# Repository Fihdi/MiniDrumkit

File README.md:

# 30hp Drumkit module

Eurorack DrumKit module with an Arduino Nano ESP32 3 channel wave-file player and analog Hi-Hat and Kick Drum sections.

The WAV Files are read from a microSD card and need to be called "1.wav", "2.wav" and "3.wav". The files need to be mono, encoded in 16-bit and have 16kHz sampling rate. You can use Audacity to export wav files in this format.

Demo Video: https://www.youtube.com/watch?v=cPHg9nKNO_o

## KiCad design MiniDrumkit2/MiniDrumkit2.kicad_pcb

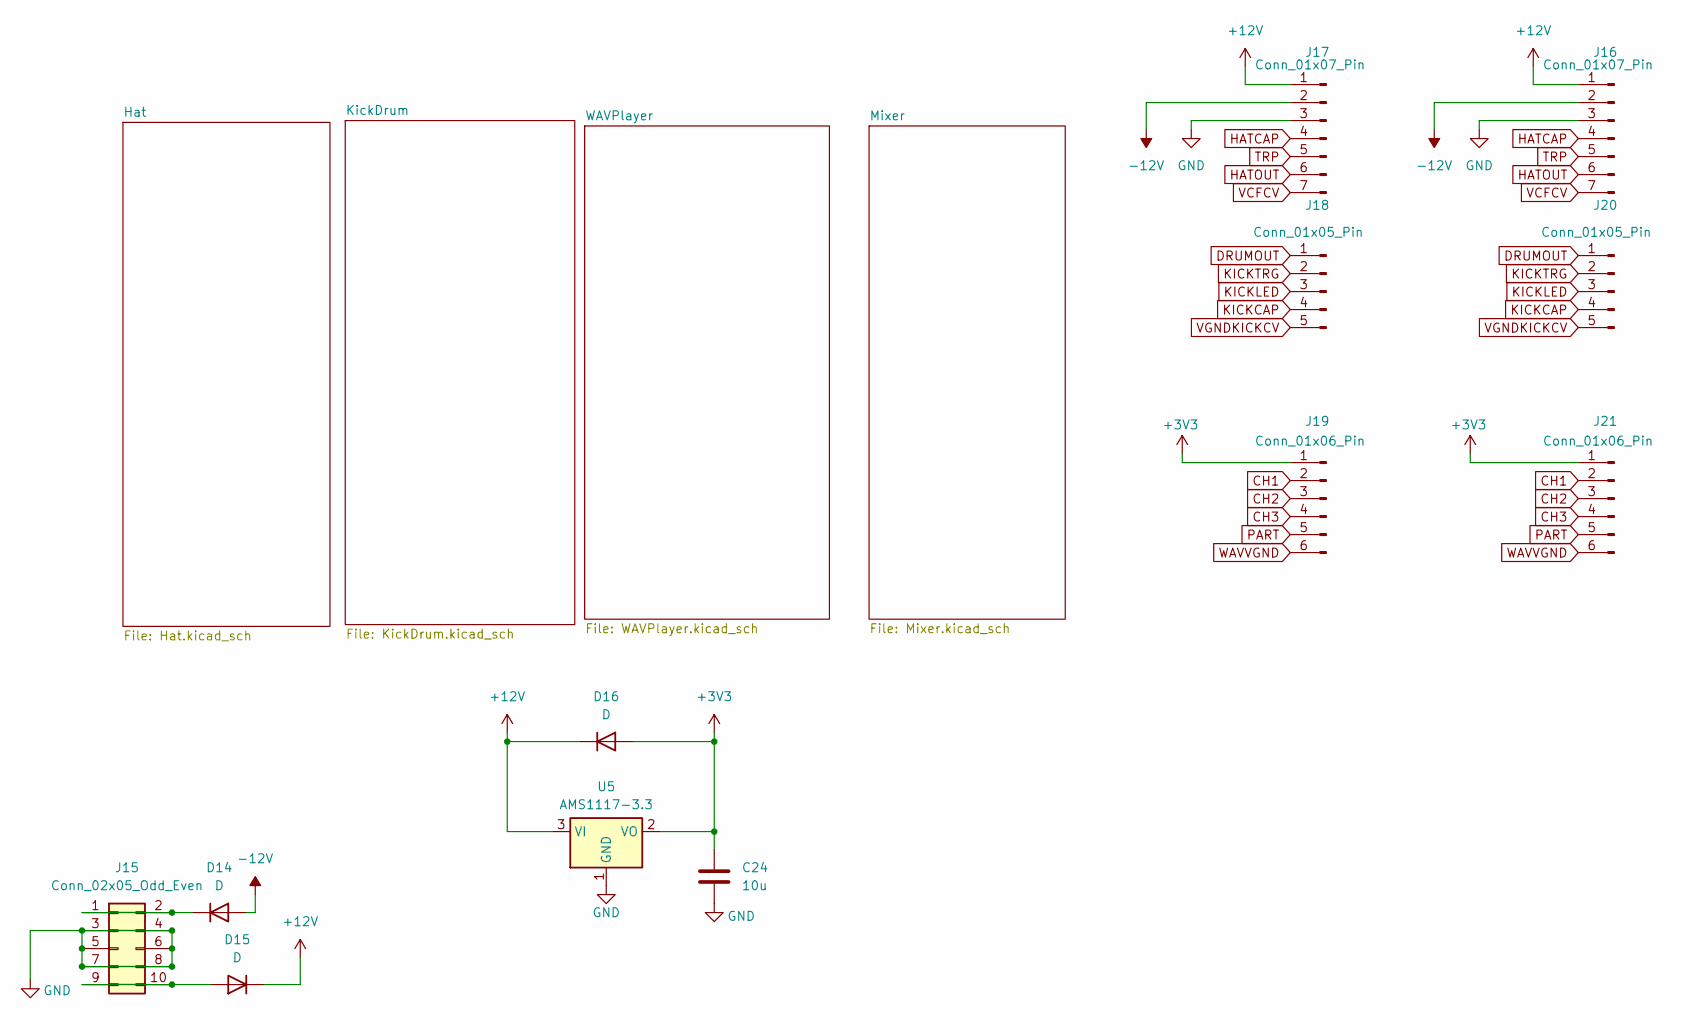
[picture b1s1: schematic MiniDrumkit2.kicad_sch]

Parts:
C24: 10u; C_1206_3216Metric
D14, D15, D16: D; D_1206_3216Metric_Pad1.42x1.75mm_HandSolder
J15: Conn_02x05_Odd_Even; IDC-Header_2x05_P2.54mm_Vertical
J16, J17: Conn_01x07_Pin; PinHeader_1x07_P2.54mm_Vertical
J18, J20: Conn_01x05_Pin; PinHeader_1x05_P2.54mm_Vertical
J19, J21: Conn_01x06_Pin; PinSocket_1x06_P2.54mm_Vertical
U5: AMS1117-3.3; SOT-223-3_TabPin2

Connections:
+3V3: C24.1, D16.2 (A), J19.1, J21.1, U5.2 (VO); also elsewhere on the board
+12V: D15.1 (K), D16.1 (K), J16.1, J17.1, U5.3 (VI); also elsewhere on the board
-12V: D14.2 (A), J16.2, J17.2; also elsewhere on the board
CH1: J19.2, J21.2; also elsewhere on the board
CH2: J19.3, J21.3; also elsewhere on the board
CH3: J19.4, J21.4; also elsewhere on the board
DRUMOUT: J18.1, J20.1; also elsewhere on the board
GND: C24.2, J15.3, J15.4, J15.5, J15.6, J15.7, J15.8, J16.3, J17.3, U5.1 (GND); also elsewhere on the board
HATCAP: J16.4, J17.4; also elsewhere on the board
HATOUT: J16.6, J17.6; also elsewhere on the board
KICKCAP: J18.4, J20.4; also elsewhere on the board
KICKLED: J18.3, J20.3; also elsewhere on the board
KICKTRG: J18.2, J20.2; also elsewhere on the board
unnamed: D14.1 (K), J15.1, J15.2
unnamed: D15.2 (A), J15.9, J15.10
PART: J19.5, J21.5; also elsewhere on the board
TRP: J16.5, J17.5; also elsewhere on the board
VCFCV: J16.7, J17.7; also elsewhere on the board
VGNDKICKCV: J18.5, J20.5; also elsewhere on the board
WAVVGND: J19.6, J21.6; also elsewhere on the board

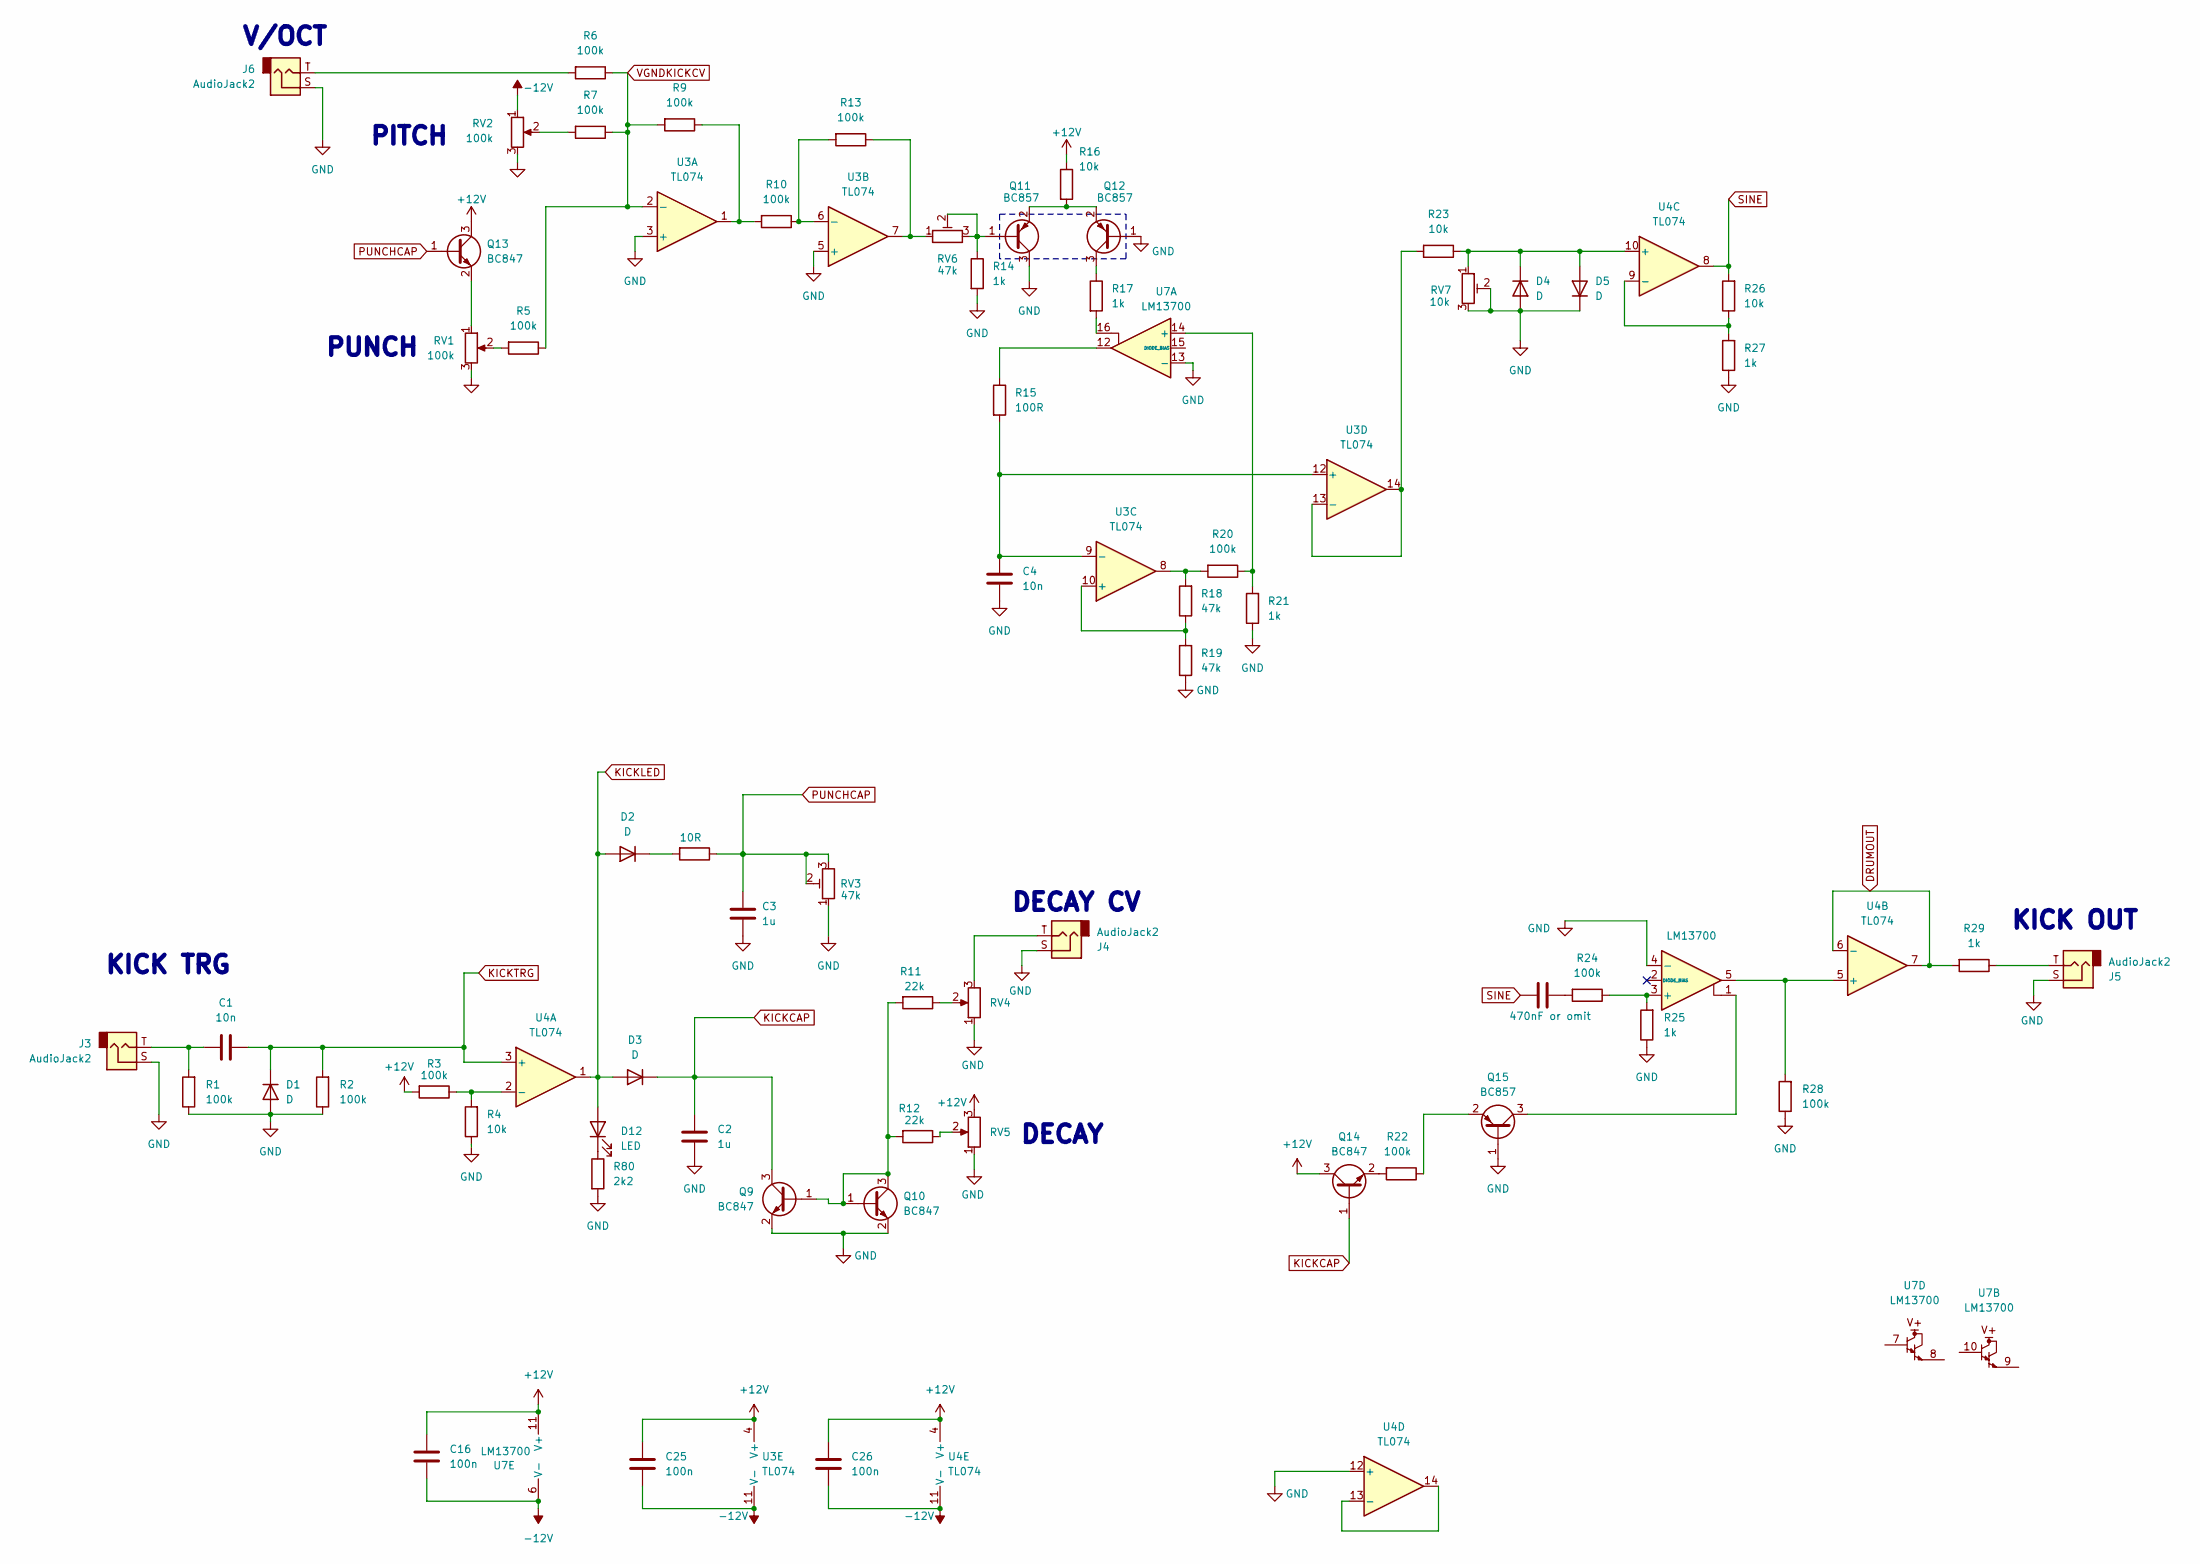
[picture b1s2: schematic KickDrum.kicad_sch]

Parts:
C1, C4: 10n; C_1206_3216Metric
C2, C3: 1u; C_1206_3216Metric
C5: 470nF or omit; C_1206_3216Metric
C16, C25, C26: 100n; C_1206_3216Metric
D1, D2, D3, D4, D5: D; D_1206_3216Metric
D12: LED; LED_D3.0mm
J3, J4, J5, J6: AudioJack2; MonoTRS
Q9, Q10, Q13, Q14: BC847; SOT-23
Q11, Q12, Q15: BC857; SOT-23
R1, R2, R3, R5, R6, R7, R9, R10, R13, R20, R22, R24, R28: 100k; R_1206_3216Metric
R4, R16, R23, R26: 10k; R_1206_3216Metric
R8: 10R; R_1206_3216Metric
R11, R12: 22k; R_1206_3216Metric
R14, R17, R21, R25, R27, R29: 1k; R_1206_3216Metric
R15: 100R; R_1206_3216Metric
R18, R19: 47k; R_1206_3216Metric
R80: 2k2; R_1206_3216Metric
RV1, RV2: 100k; Potentiometer_Alpha_RD901F-40-00D_Single_Vertical_CircularH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
RV3, RV6: 47k; Potentiometer_ACP_CA9-H5_Horizontal
RV4, RV5: R_Potentiometer; Potentiometer_Alpha_RD901F-40-00D_Single_Vertical_CircularH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
RV7: 10k; Potentiometer_ACP_CA9-H5_Horizontal
U3, U4: TL074; SOIC-14_3.9x8.7mm_P1.27mm
U7: LM13700; SOIC-16_3.9x9.9mm_P1.27mm

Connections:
+12V: C16.1, C25.1, C26.1, Q13.3 (C), Q14.3 (C), R3.2, R16.1, RV5.3, U3.4 (V+), U4.4 (V+), U7.11 (V+); also elsewhere on the board
-12V: C16.2, C25.2, C26.2, RV2.1, U3.11 (V-), U4.11 (V-), U7.6 (V-); also elsewhere on the board
DRUMOUT: R29.2, U4.6 (-), U4.7; also elsewhere on the board
GND: C2.2, C3.2, C4.2, D1.2 (A), D4.2 (A), D5.1 (K), J3.S, J4.S, J5.S, J6.S, Q9.2 (E), Q10.2 (E), Q11.3 (C), Q12.1 (B), Q15.1 (B), R1.1, R2.1, R4.1, R14.2, R19.1, R21.1, R25.1, R27.1, R28.1, R80.2, RV1.3, RV2.3, RV3.1, RV4.1, RV5.1, RV7.2, RV7.3, U3.3 (+), U3.5 (+), U4.12 (+), U7.4 (-), U7.13 (-); also elsewhere on the board
KICKCAP: C2.1, D3.1 (K), Q9.3 (C), Q14.1 (B); also elsewhere on the board
KICKLED: D2.2 (A), D3.2 (A), D12.2 (A), U4.1; also elsewhere on the board
KICKTRG: C1.2, D1.1 (K), R2.2, U4.3 (+); also elsewhere on the board
unnamed: C1.1, J3.T, R1.2
unnamed: C5.2, R24.2
unnamed: D2.1 (K), R8.2
unnamed: D4.1 (K), D5.2 (A), R23.1, RV7.1, U4.10 (+)
unnamed: D12.1 (K), R80.1
unnamed: J4.T, RV4.3
unnamed: J5.T, R29.1
unnamed: J6.T, R6.2
unnamed: Q9.1 (B), Q10.1 (B), Q10.3 (C), R11.2, R12.2
unnamed: Q11.1 (B), R14.1, RV6.2, RV6.3
unnamed: Q11.2 (E), Q12.2 (E), R16.2
unnamed: Q12.3 (C), R17.1
unnamed: Q13.2 (E), RV1.1
unnamed: Q14.2 (E), R22.2
unnamed: Q15.3 (C), U7.1
unnamed: Q15.2 (E), R22.1
unnamed: R5.2, RV1.2
unnamed: R7.2, RV2.2
unnamed: R9.1, R10.2, U3.1
unnamed: R11.1, RV4.2
unnamed: R12.1, RV5.2
unnamed: R13.1, RV6.1, U3.7
unnamed: R15.1, U7.12
unnamed: R17.2, U7.16
unnamed: R18.2, R20.2, U3.8
unnamed: R10.1, R13.2, U3.6 (-)
unnamed: R18.1, R19.2, U3.10 (+)
unnamed: C4.1, R15.2, U3.9 (-), U3.12 (+)
unnamed: R23.2, U3.13 (-), U3.14
unnamed: R3.1, R4.2, U4.2 (-)
unnamed: R28.2, U4.5 (+), U7.5
unnamed: R26.1, R27.2, U4.9 (-)
unnamed: U4.13 (-), U4.14
unnamed: R20.1, R21.2, U7.14 (+)
unnamed: R24.1, R25.2, U7.3 (+)
PUNCHCAP: C3.1, Q13.1 (B), R8.1, RV3.2, RV3.3
SINE: C5.1, R26.2, U4.8
VGNDKICKCV: R5.1, R6.1, R7.1, R9.2, U3.2 (-); also elsewhere on the board

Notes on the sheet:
DECAY CV
KICK OUT
PITCH
V/OCT
DECAY
KICK TRG
PUNCH

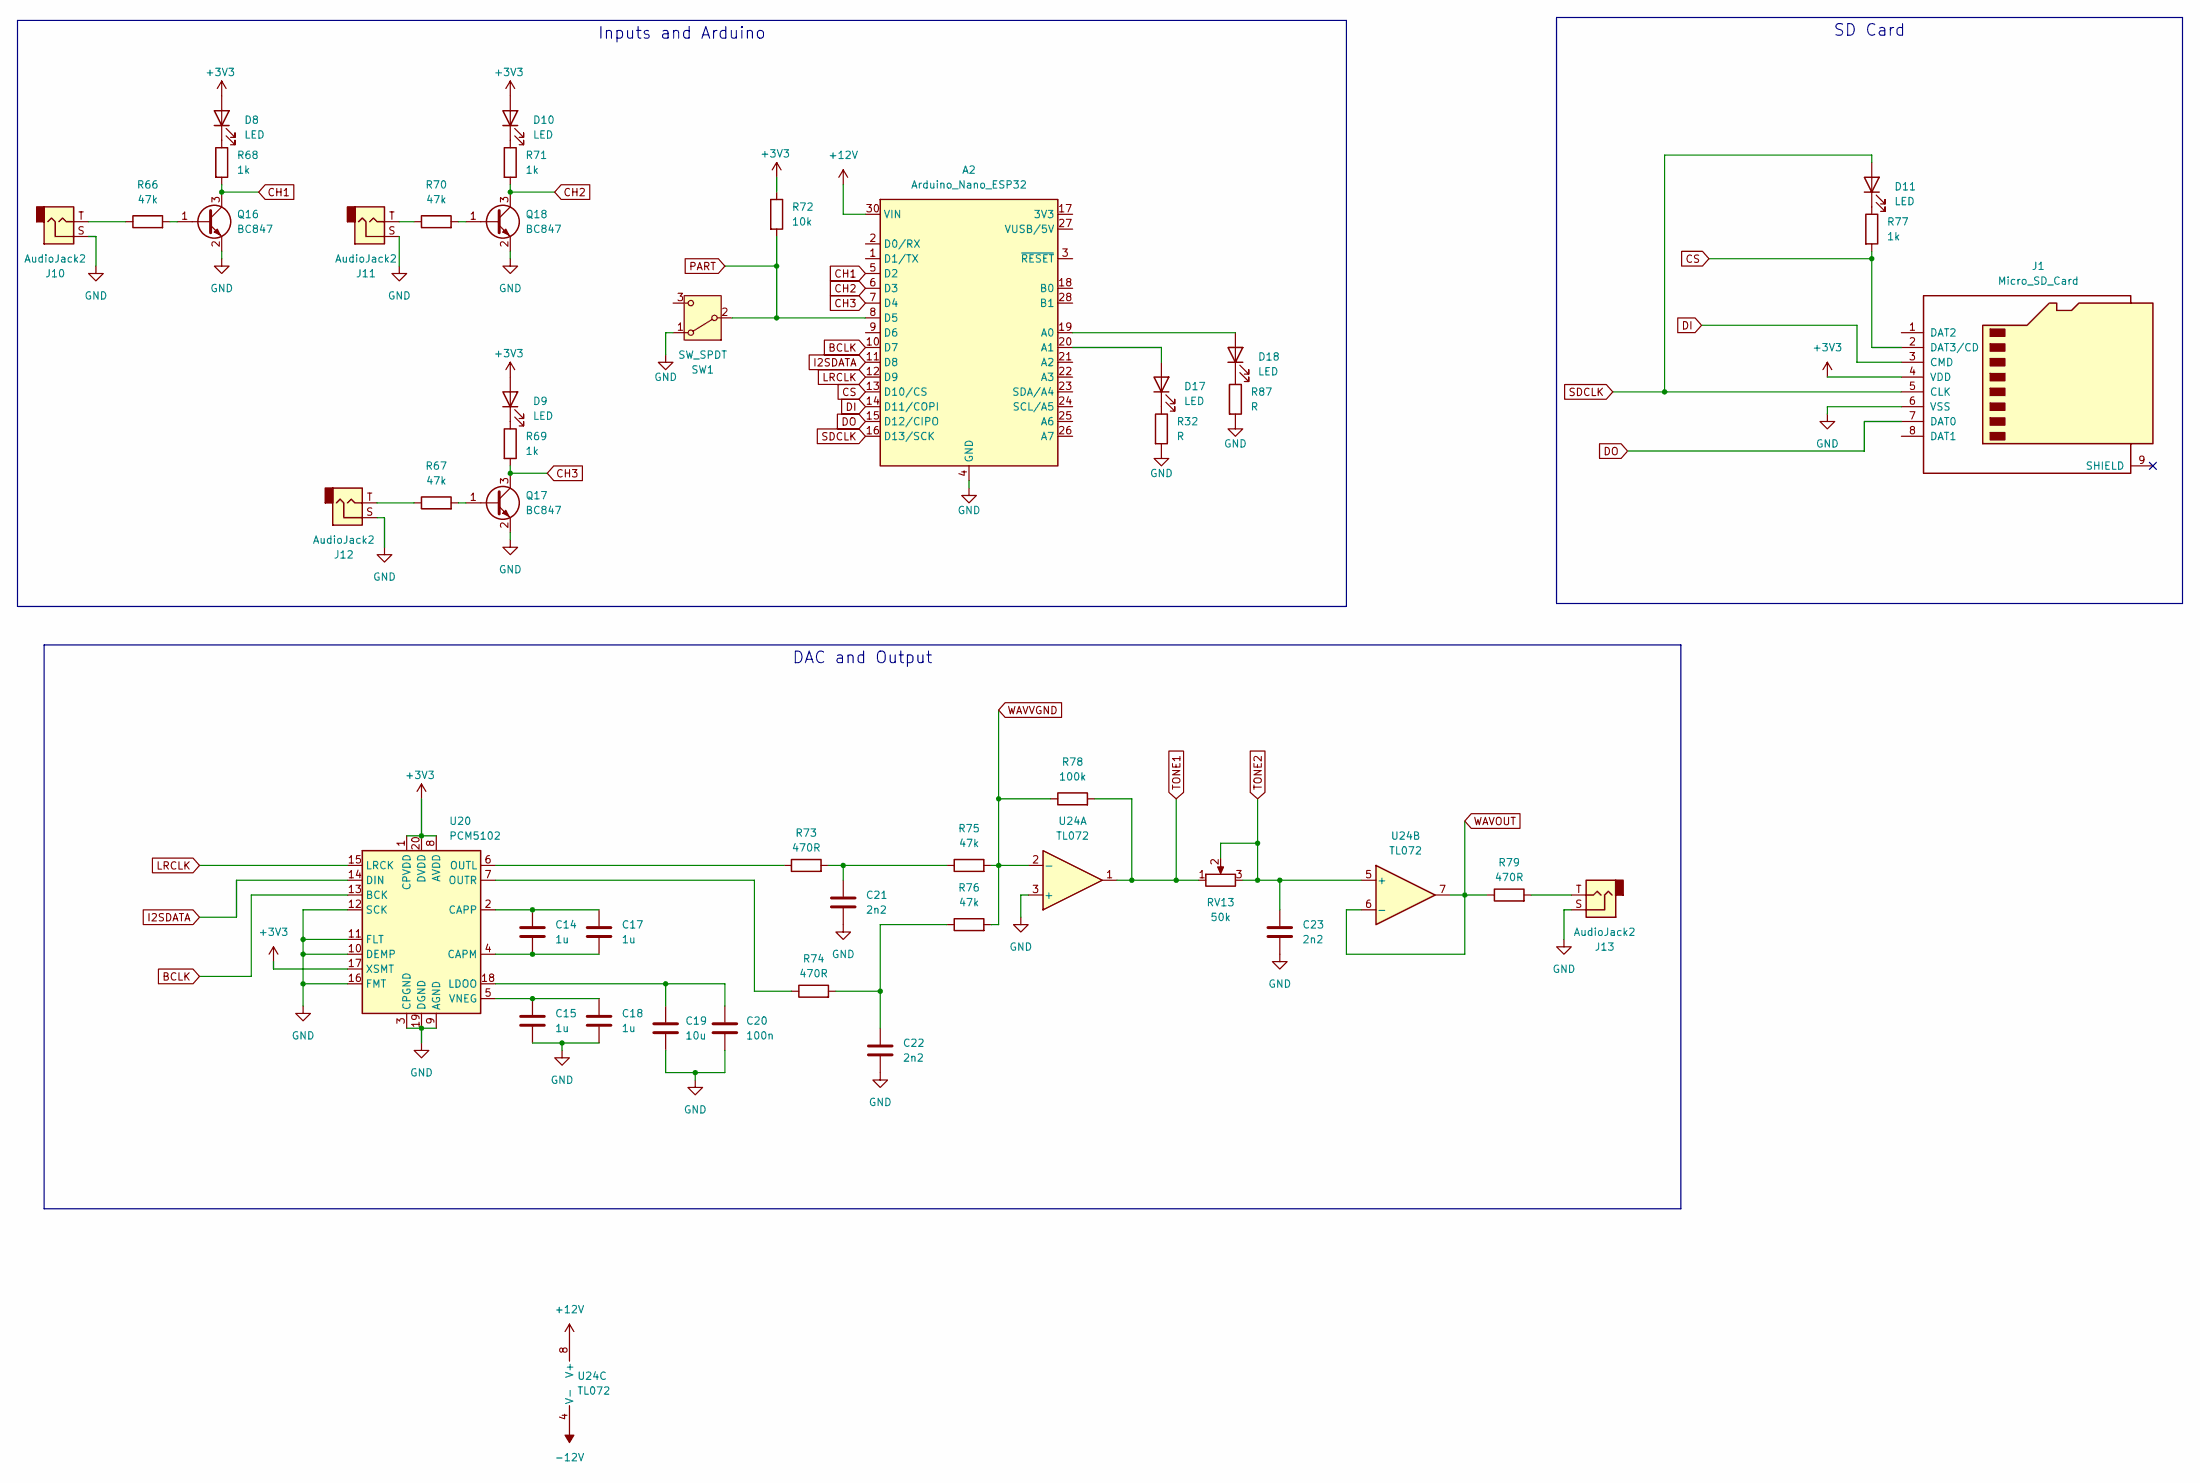
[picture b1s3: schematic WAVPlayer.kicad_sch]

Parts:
A2: Arduino_Nano_ESP32; Arduino_Nano
C14, C15, C17, C18: 1u; C_1206_3216Metric
C19: 10u; C_1206_3216Metric
C20: 100n; C_1206_3216Metric
C21, C22, C23: 2n2; C_1206_3216Metric
D8, D9, D10, D11, D17, D18: LED; LED_D3.0mm
J1: Micro_SD_Card; microSD_HC_Molex_47219-2001
J10, J11, J12, J13: AudioJack2; MonoTRS
Q16, Q17, Q18: BC847; SOT-23
R32, R87: R; R_1206_3216Metric
R66, R67, R70, R75, R76: 47k; R_1206_3216Metric
R68, R69, R71, R77: 1k; R_1206_3216Metric
R72: 10k; R_1206_3216Metric
R73, R74, R79: 470R; R_1206_3216Metric
R78: 100k; R_1206_3216Metric
RV13: 50k; Potentiometer_Alpha_RD901F-40-00D_Single_Vertical_CircularH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
SW1: SW_SPDT; Switch
U20: PCM5102; TSSOP-20_4.4x6.5mm_P0.65mm
U24: TL072; SOIC-8_3.9x4.9mm_P1.27mm

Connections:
+3V3: D8.2 (A), D9.2 (A), D10.2 (A), J1.4 (VDD), R72.1, U20.1 (CPVDD), U20.8 (AVDD), U20.17 (XSMT), U20.20 (DVDD); also elsewhere on the board
+12V: A2.30 (VIN), U24.8 (V+); also elsewhere on the board
-12V: U24.4 (V-); also elsewhere on the board
BCLK: A2.10 (D7), U20.13 (BCK)
CH1: A2.5 (D2), Q16.3 (C), R68.2; also elsewhere on the board
CH2: A2.6 (D3), Q18.3 (C), R71.2; also elsewhere on the board
CH3: A2.7 (D4), Q17.3 (C), R69.2; also elsewhere on the board
CS: A2.13 (D10/CS), J1.2 (DAT3/CD), R77.2
DI: A2.14 (D11/COPI), J1.3 (CMD)
DO: A2.15 (D12/CIPO), J1.7 (DAT0)
GND: A2.4 (GND), A2.29 (GND), C15.2, C18.2, C19.2, C20.2, C21.2, C22.2, C23.2, J1.6 (VSS), J10.S, J11.S, J12.S, J13.S, Q16.2 (E), Q17.2 (E), Q18.2 (E), R32.2, R87.2, SW1.1 (A), U20.3 (CPGND), U20.9 (AGND), U20.10 (DEMP), U20.11 (FLT), U20.12 (SCK), U20.16 (FMT), U20.19 (DGND), U24.3 (+); also elsewhere on the board
I2SDATA: A2.11 (D8), U20.14 (DIN)
LRCLK: A2.12 (D9), U20.15 (LRCK)
unnamed: A2.19 (A0), D18.2 (A)
unnamed: A2.20 (A1), D17.2 (A)
unnamed: C21.1, R73.2, R75.1
unnamed: C22.1, R74.2, R76.1
unnamed: D8.1 (K), R68.1
unnamed: D9.1 (K), R69.1
unnamed: D10.1 (K), R71.1
unnamed: D11.1 (K), R77.1
unnamed: D17.1 (K), R32.1
unnamed: D18.1 (K), R87.1
unnamed: J10.T, R66.1
unnamed: J11.T, R70.1
unnamed: J12.T, R67.1
unnamed: J13.T, R79.2
unnamed: Q16.1 (B), R66.2
unnamed: Q17.1 (B), R67.2
unnamed: Q18.1 (B), R70.2
unnamed: C14.2, C17.2, U20.4 (CAPM)
unnamed: C14.1, C17.1, U20.2 (CAPP)
unnamed: C19.1, C20.1, U20.18 (LDOO)
unnamed: R73.1, U20.6 (OUTL)
unnamed: R74.1, U20.7 (OUTR)
unnamed: C15.1, C18.1, U20.5 (VNEG)
PART: A2.8 (D5), R72.2, SW1.2 (B); also elsewhere on the board
SDCLK: A2.16 (D13/SCK), D11.2 (A), J1.5 (CLK)
TONE1: R78.2, RV13.1, U24.1
TONE2: C23.1, RV13.2, RV13.3, U24.5 (+)
WAVOUT: R79.1, U24.6 (-), U24.7; also elsewhere on the board
WAVVGND: R75.2, R76.2, R78.1, U24.2 (-); also elsewhere on the board

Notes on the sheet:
DAC and Output
SD Card
Inputs and Arduino

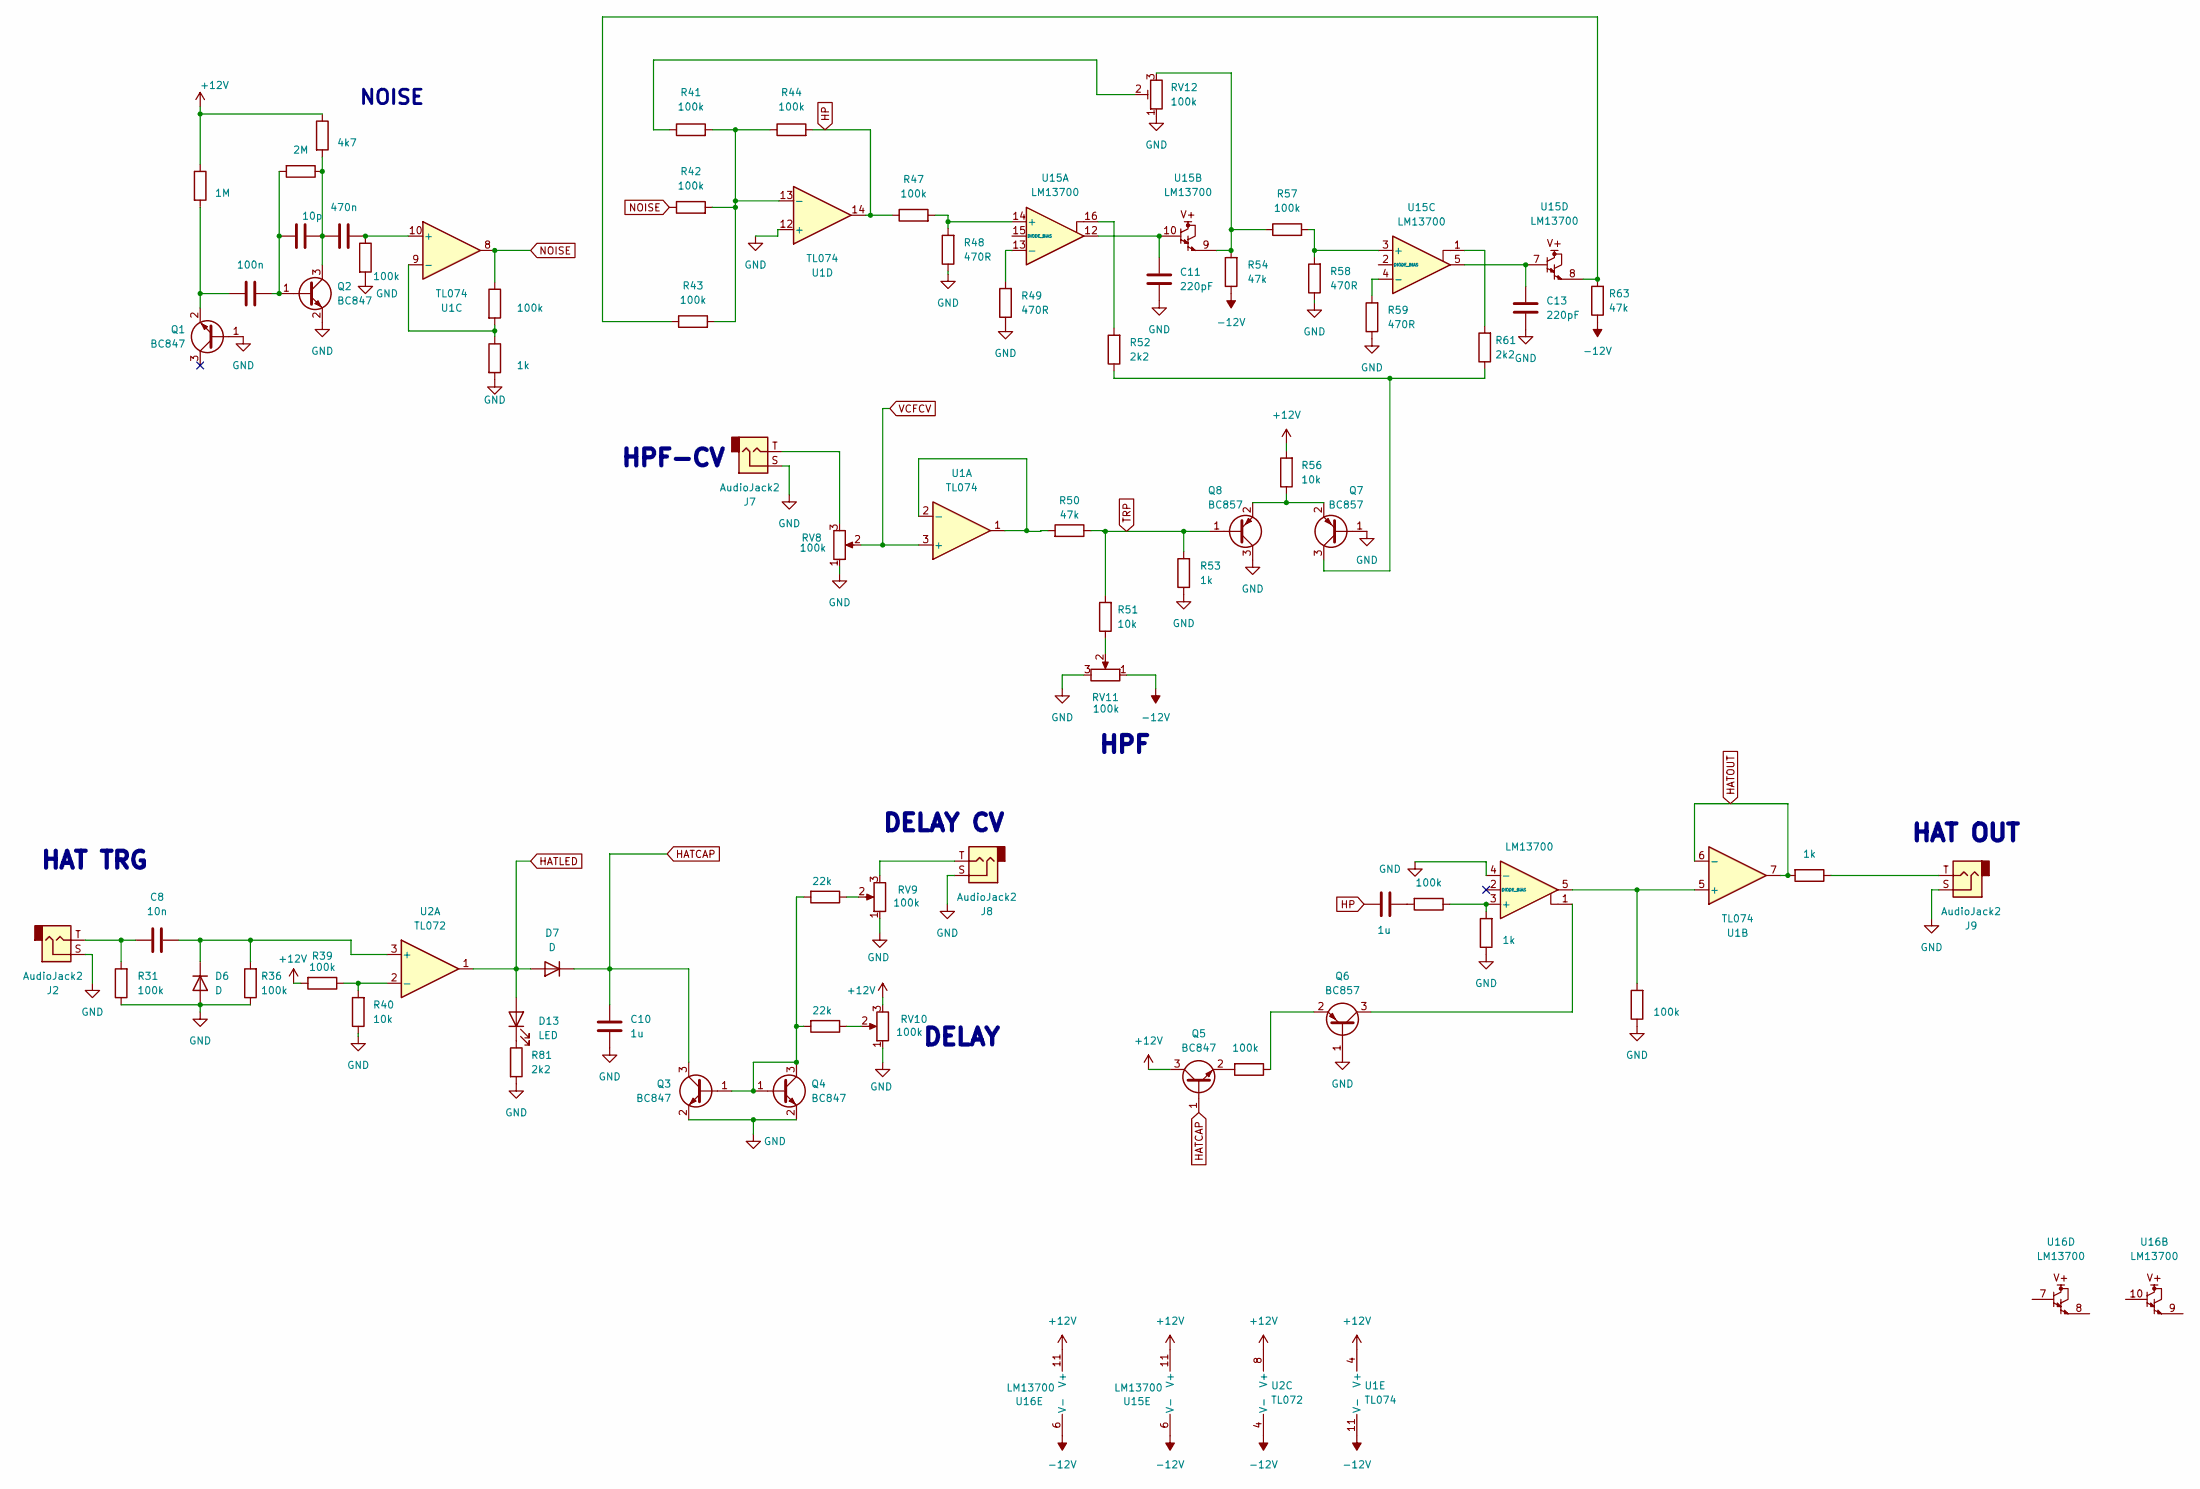
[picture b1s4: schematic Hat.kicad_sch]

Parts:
C6: 100n; C_1206_3216Metric
C7: 10p; C_1206_3216Metric
C8: 10n; C_1206_3216Metric
C9: 470n; C_1206_3216Metric
C10, C12: 1u; C_1206_3216Metric
C11, C13: 220pF; C_1206_3216Metric
D6, D7: D; D_1206_3216Metric
D13: LED; LED_D3.0mm
J2, J7, J8, J9: AudioJack2; MonoTRS
Q1, Q2, Q3, Q4, Q5: BC847; SOT-23
Q6, Q7, Q8: BC857; SOT-23
R30: 1M; R_1206_3216Metric
R31, R35, R36, R37, R39, R41, R42, R43, R44, R47, R55, R57, R60, R64: 100k; R_1206_3216Metric
R33: 2M; R_1206_3216Metric
R34: 4k7; R_1206_3216Metric
R38, R53, R62, R65: 1k; R_1206_3216Metric
R40, R51, R56: 10k; R_1206_3216Metric
R45, R46: 22k; R_1206_3216Metric
R48, R49, R58, R59: 470R; R_1206_3216Metric
R50, R54, R63: 47k; R_1206_3216Metric
R52, R61, R81: 2k2; R_1206_3216Metric
RV8, RV9, RV10, RV11: 100k; Potentiometer_Alpha_RD901F-40-00D_Single_Vertical_CircularH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
RV12: 100k; Potentiometer_ACP_CA9-H5_Horizontal
U1: TL074; SOIC-14_3.9x8.7mm_P1.27mm
U2: TL072; SOIC-8_5.3x6.2mm_P1.27mm
U15, U16: LM13700; SOIC-16_3.9x9.9mm_P1.27mm

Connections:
+12V: Q5.3 (C), R30.1, R34.1, R39.2, R56.2, RV10.3, U1.4 (V+), U2.8 (V+), U15.11 (V+), U16.11 (V+); also elsewhere on the board
-12V: R54.1, R63.1, RV11.1, U1.11 (V-), U2.4 (V-), U15.6 (V-), U16.6 (V-); also elsewhere on the board
GND: C10.2, C11.2, C13.2, D6.2 (A), J2.S, J7.S, J8.S, J9.S, Q1.1 (B), Q2.2 (E), Q3.2 (E), Q4.2 (E), Q6.1 (B), Q7.1 (B), Q8.3 (C), R31.1, R35.2, R36.1, R38.2, R40.1, R48.1, R49.1, R53.1, R58.1, R59.1, R62.1, R64.1, R81.2, RV8.1, RV9.1, RV10.1, RV11.3, RV12.1, U1.12 (+), U16.4 (-); also elsewhere on the board
HATCAP: C10.1, D7.1 (K), Q3.3 (C), Q5.1 (B); also elsewhere on the board
HATLED: D7.2 (A), D13.2 (A), U2.1
HATOUT: R65.2, U1.6 (-), U1.7; also elsewhere on the board
HP: C12.1, R44.2, R47.1, U1.14
NOISE: R37.1, R42.1, U1.8
unnamed: C8.1, J2.T, R31.2
unnamed: C11.1, U15.10, U15.12
unnamed: C12.2, R60.2
unnamed: C13.1, U15.5, U15.7
unnamed: C8.2, D6.1 (K), R36.2, U2.3 (+)
unnamed: D13.1 (K), R81.1
unnamed: J7.T, RV8.3
unnamed: J8.T, RV9.3
unnamed: J9.T, R65.1
unnamed: C6.1, Q1.2 (E), R30.2
unnamed: C6.2, C7.1, Q2.1 (B), R33.2
unnamed: C7.2, C9.1, Q2.3 (C), R33.1, R34.2
unnamed: Q3.1 (B), Q4.1 (B), Q4.3 (C), R45.2, R46.2
unnamed: Q5.2 (E), R55.2
unnamed: Q6.3 (C), U16.1
unnamed: Q6.2 (E), R55.1
unnamed: Q7.3 (C), R52.1, R61.1
unnamed: Q7.2 (E), Q8.2 (E), R56.1
unnamed: R41.1, RV12.2
unnamed: R43.1, R63.2, U15.8
unnamed: R45.1, RV9.2
unnamed: R46.1, RV10.2
unnamed: R51.1, RV11.2
unnamed: R52.2, U15.16
unnamed: R61.2, U15.1
unnamed: R50.2, U1.1, U1.2 (-)
unnamed: R64.2, U1.5 (+), U16.5
unnamed: C9.2, R35.1, U1.10 (+)
unnamed: R37.2, R38.1, U1.9 (-)
unnamed: R41.2, R42.2, R43.2, R44.1, U1.13 (-)
unnamed: R39.1, R40.2, U2.2 (-)
unnamed: R47.2, R48.2, U15.14 (+)
unnamed: R49.2, U15.13 (-)
unnamed: R57.2, R58.2, U15.3 (+)
unnamed: R59.2, U15.4 (-)
unnamed: R60.1, R62.2, U16.3 (+)
RES: R54.2, R57.1, RV12.3, U15.9
TRP: Q8.1 (B), R50.1, R51.2, R53.2; also elsewhere on the board
VCFCV: RV8.2, U1.3 (+); also elsewhere on the board

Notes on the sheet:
NOISE
HPF-CV
HPF
DELAY CV
DELAY
HAT OUT
HAT TRG

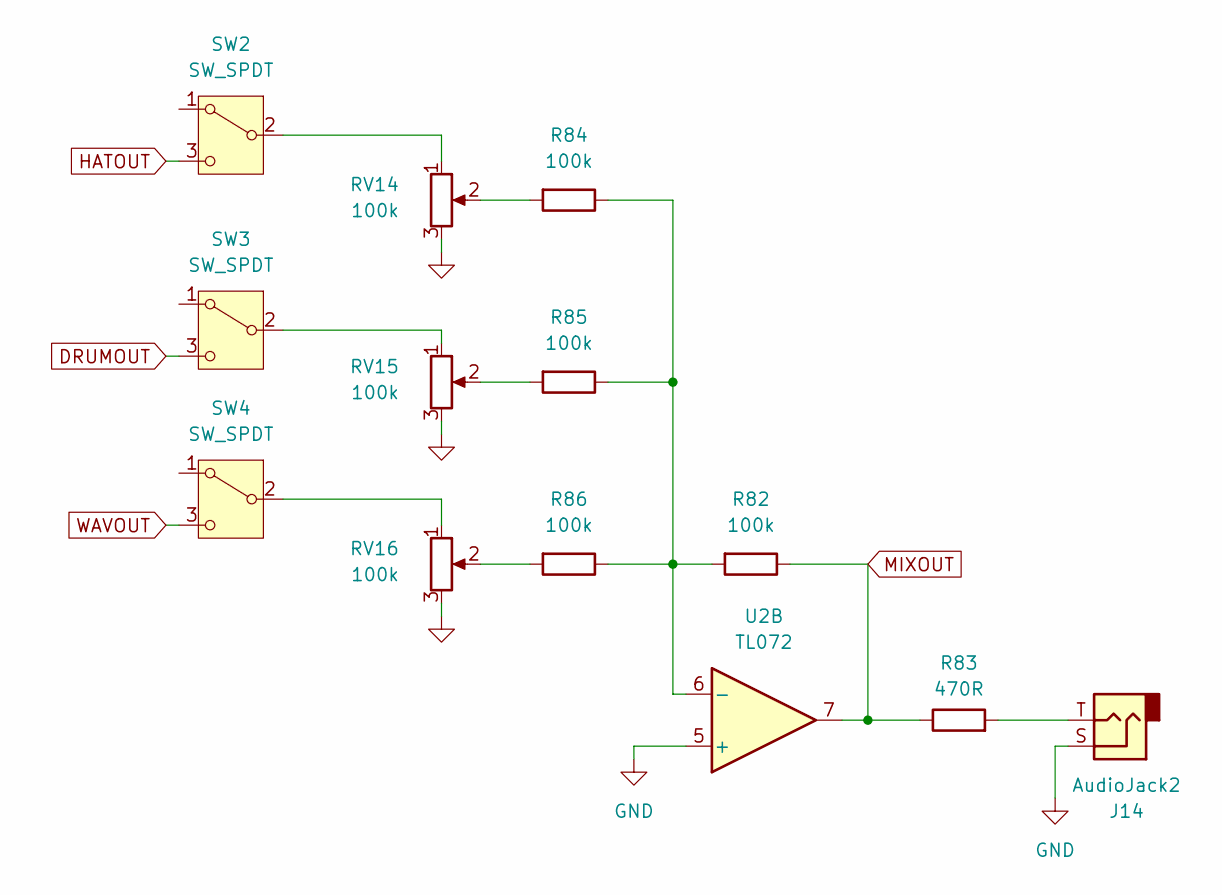
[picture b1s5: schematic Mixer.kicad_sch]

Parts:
J14: AudioJack2; MonoTRS
R82, R84, R85, R86: 100k; R_1206_3216Metric
R83: 470R; R_1206_3216Metric
RV14, RV15, RV16: 100k; Potentiometer_Alpha_RD901F-40-00D_Single_Vertical_CircularH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
SW2, SW3, SW4: SW_SPDT; Switch
U2: TL072; SOIC-8_5.3x6.2mm_P1.27mm

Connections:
DRUMOUT: SW3.3 (C); also elsewhere on the board
GND: J14.S, RV14.3, RV15.3, RV16.3, U2.5 (+); also elsewhere on the board
HATOUT: SW2.3 (C); also elsewhere on the board
MIXOUT: R82.1, R83.1, U2.7
unnamed: J14.T, R83.2
unnamed: R84.2, RV14.2
unnamed: R85.2, RV15.2
unnamed: R86.2, RV16.2
unnamed: RV14.1, SW2.2 (B)
unnamed: RV15.1, SW3.2 (B)
unnamed: RV16.1, SW4.2 (B)
unnamed: R82.2, R84.1, R85.1, R86.1, U2.6 (-)
WAVOUT: SW4.3 (C); also elsewhere on the board

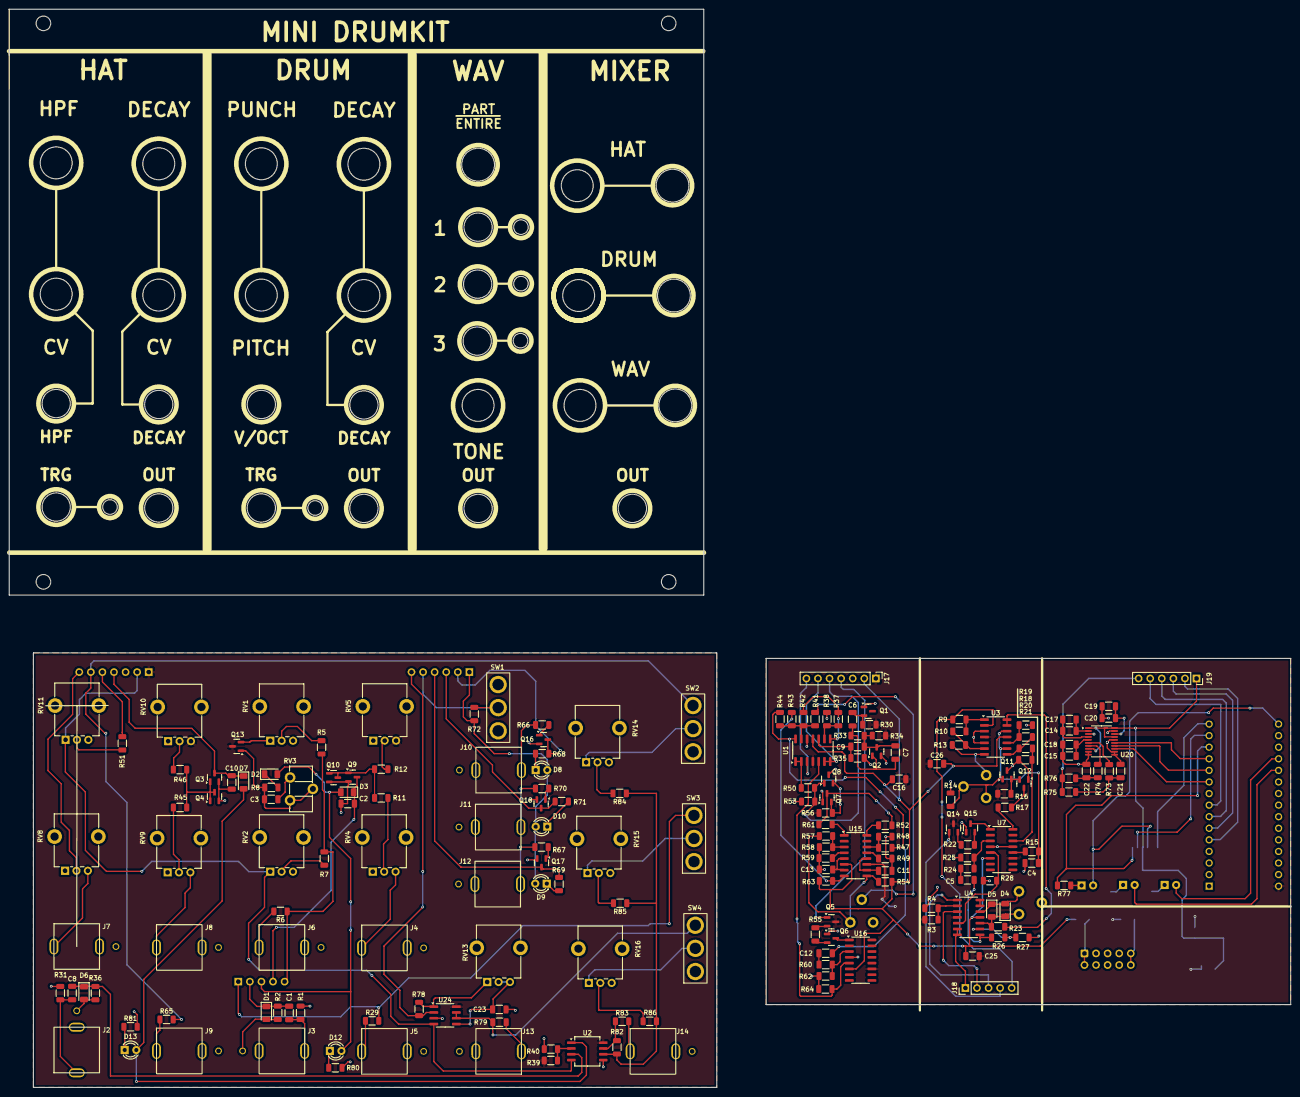
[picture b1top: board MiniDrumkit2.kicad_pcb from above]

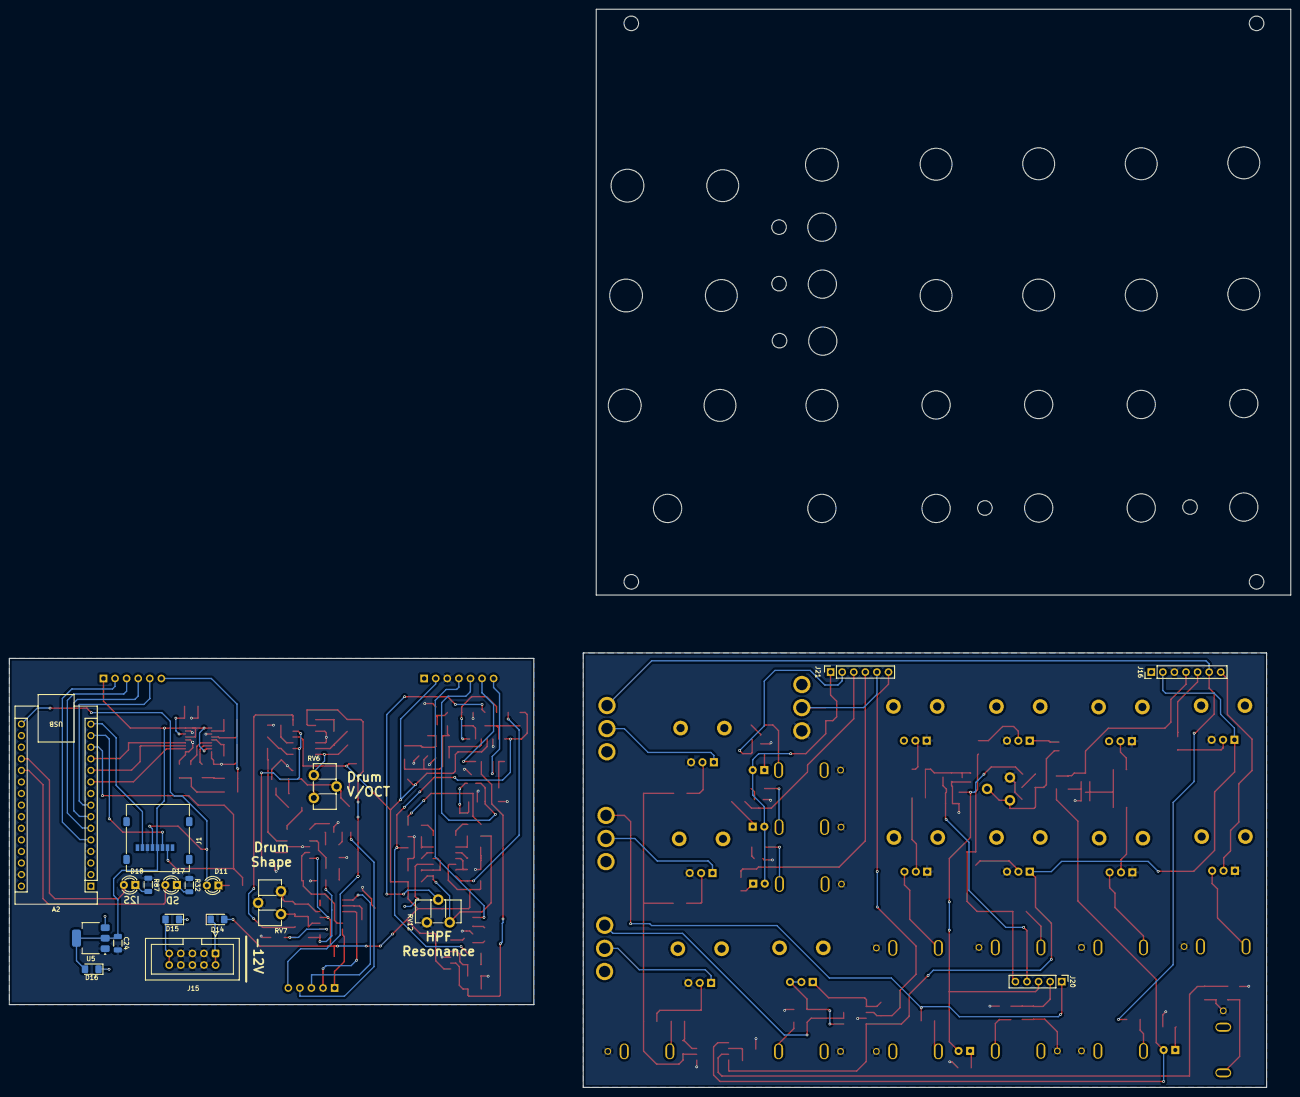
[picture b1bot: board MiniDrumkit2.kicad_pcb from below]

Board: 2 copper layers, 281.1 x 236.5 mm, 201 parts (19 on the bottom side), 139 nets.
